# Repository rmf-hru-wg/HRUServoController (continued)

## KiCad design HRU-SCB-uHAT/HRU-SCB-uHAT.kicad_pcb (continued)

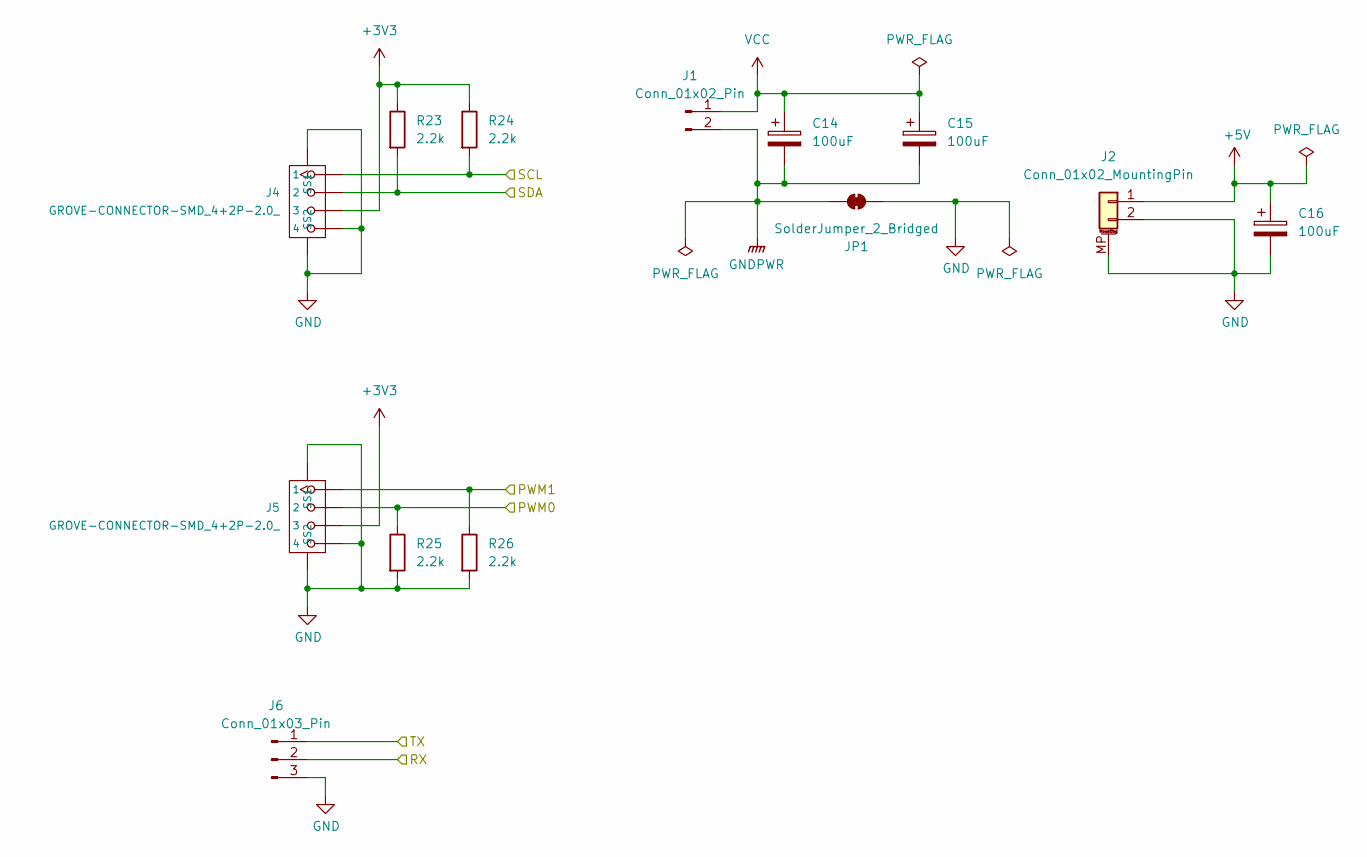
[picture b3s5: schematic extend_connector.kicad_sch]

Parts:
C14, C15, C16: 100uF; CP_EIA-6032-28_Kemet-C_HandSolder
J1: Conn_01x02_Pin; SolderWire-1.5sqmm_1x02_P7.8mm_D1.7mm_OD3.9mm
J2: Conn_01x02_MountingPin; JST_PH_B2B-PH-SM4-TB_1x02-1MP_P2.00mm_Vertical
J4, J5: GROVE-CONNECTOR-SMD_4+2P-2.0_; GROVE-HW4-SMD-2.0
J6: Conn_01x03_Pin; PinHeader_1x03_P2.54mm_Vertical
JP1: SolderJumper_2_Bridged; SolderJumper-2_P1.3mm_Bridged_Pad1.0x1.5mm
R23, R24, R25, R26: 2.2k; R_0603_1608Metric_Pad0.98x0.95mm_HandSolder

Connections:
+3V3: J4.3, J5.3, R23.1, R24.1; also elsewhere on the board
+5V: C16.1, J2.1; also elsewhere on the board
/GPIO2/SDA1: J4.2, R23.2; also elsewhere on the board
/GPIO3/SCL1: J4.1, R24.2; also elsewhere on the board
/GPIO12/PWM0: J5.2, R25.1; also elsewhere on the board
/GPIO13/PWM1: J5.1, R26.1; also elsewhere on the board
/GPIO14/TXD0: J6.1; also elsewhere on the board
/GPIO15/RXD0: J6.2; also elsewhere on the board
GND: C16.2, J2.2, J2.MP (MountPin), J4.4, J4.SS1, J4.SS2, J5.4, J5.SS1, J5.SS2, J6.3, JP1.2 (B), R25.2, R26.2; also elsewhere on the board
GNDPWR: C14.2, C15.2, J1.2, JP1.1 (A); also elsewhere on the board
VCC: C14.1, C15.1, J1.1; also elsewhere on the board

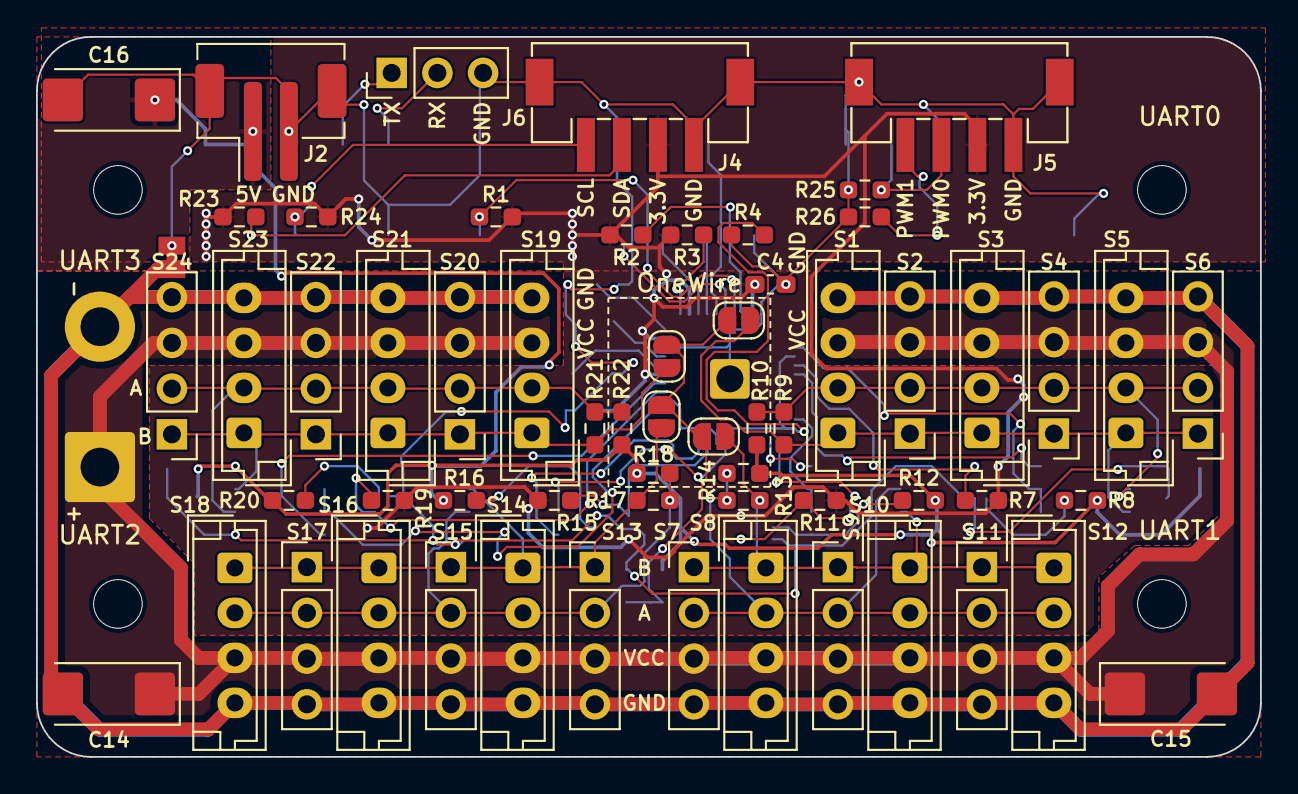
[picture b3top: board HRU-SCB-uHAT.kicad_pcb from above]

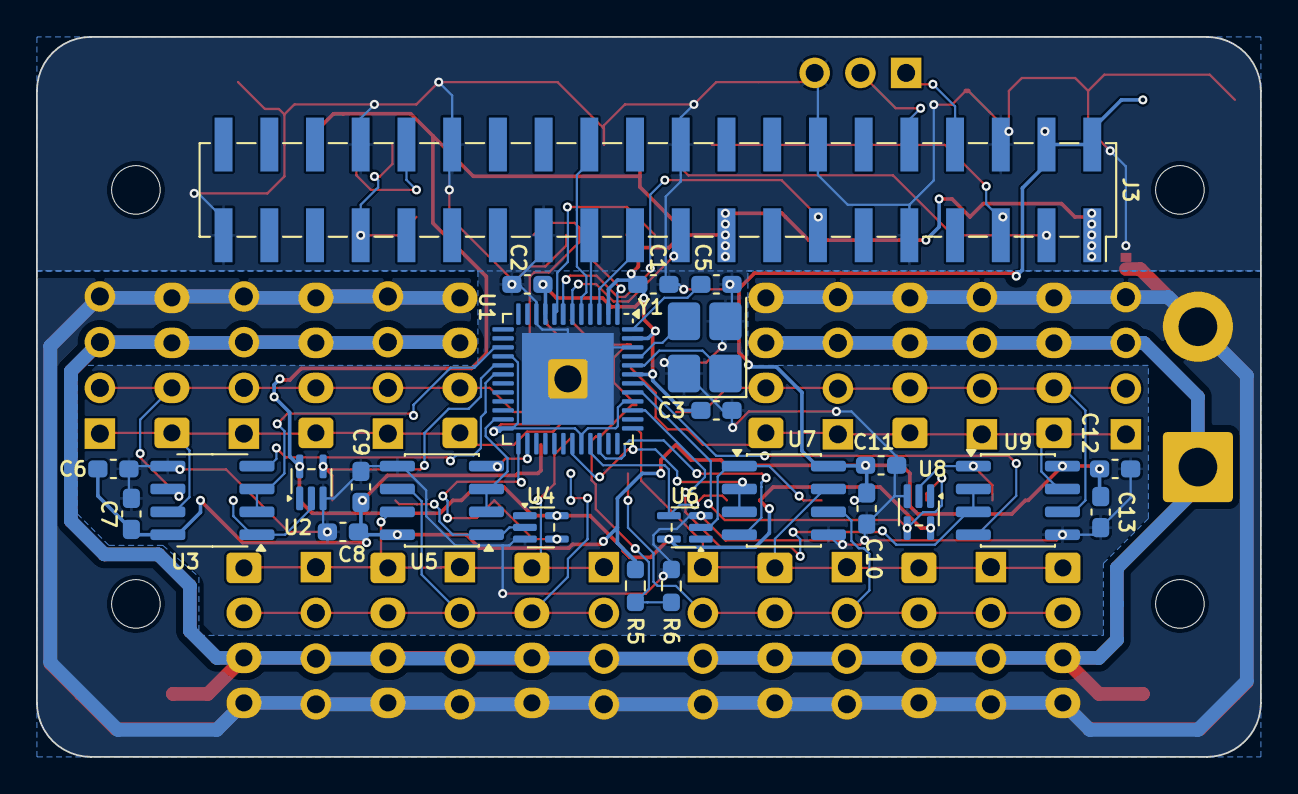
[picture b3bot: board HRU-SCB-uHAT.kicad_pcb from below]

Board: 2 copper layers, 68.0 x 40.0 mm, 91 parts (25 on the bottom side), 47 nets.

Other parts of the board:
MH1, MH2, MH3, MH4: MountingHole_2.7mm_M2.5

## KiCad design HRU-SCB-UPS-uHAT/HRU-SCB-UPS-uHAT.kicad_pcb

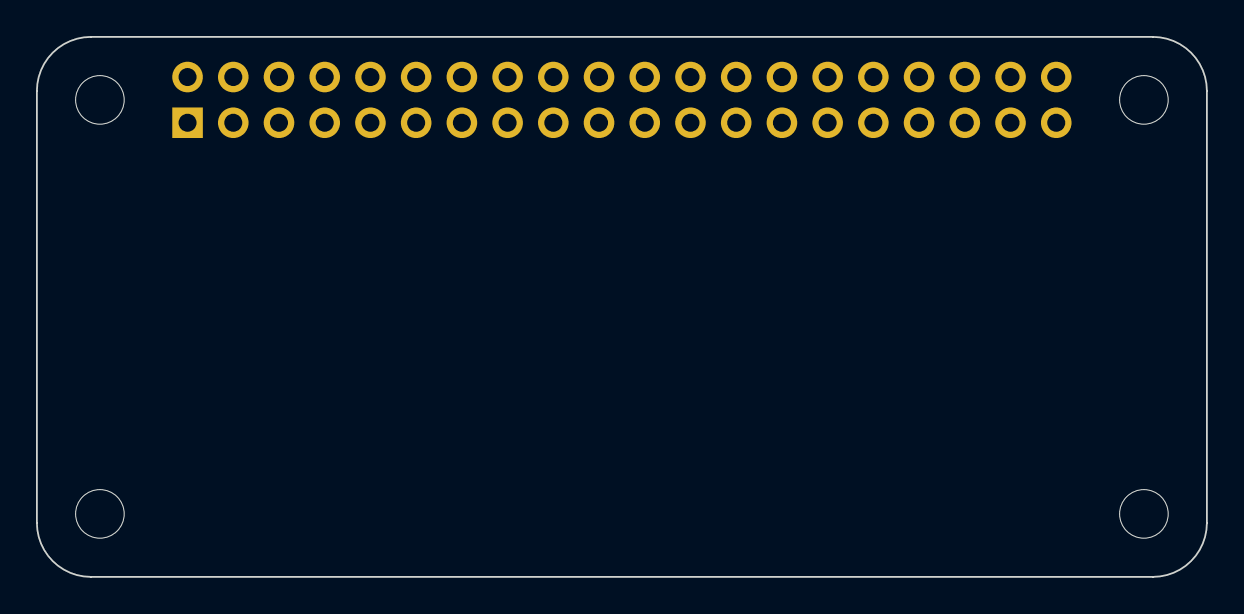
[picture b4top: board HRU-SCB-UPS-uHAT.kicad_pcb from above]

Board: 2 copper layers, 65.0 x 30.0 mm, 5 parts (1 on the bottom side), 3 nets, no tracks yet.

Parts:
J1: GPIO; PinSocket_2x20_P2.54mm_Vertical
MH1, MH2, MH3, MH4: MountingHole_2.7mm_M2.5

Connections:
+3V3: J1.1, J1.17
+5V: J1.2, J1.4
GND: J1.6, J1.9, J1.14, J1.20, J1.25, J1.30, J1.34, J1.39

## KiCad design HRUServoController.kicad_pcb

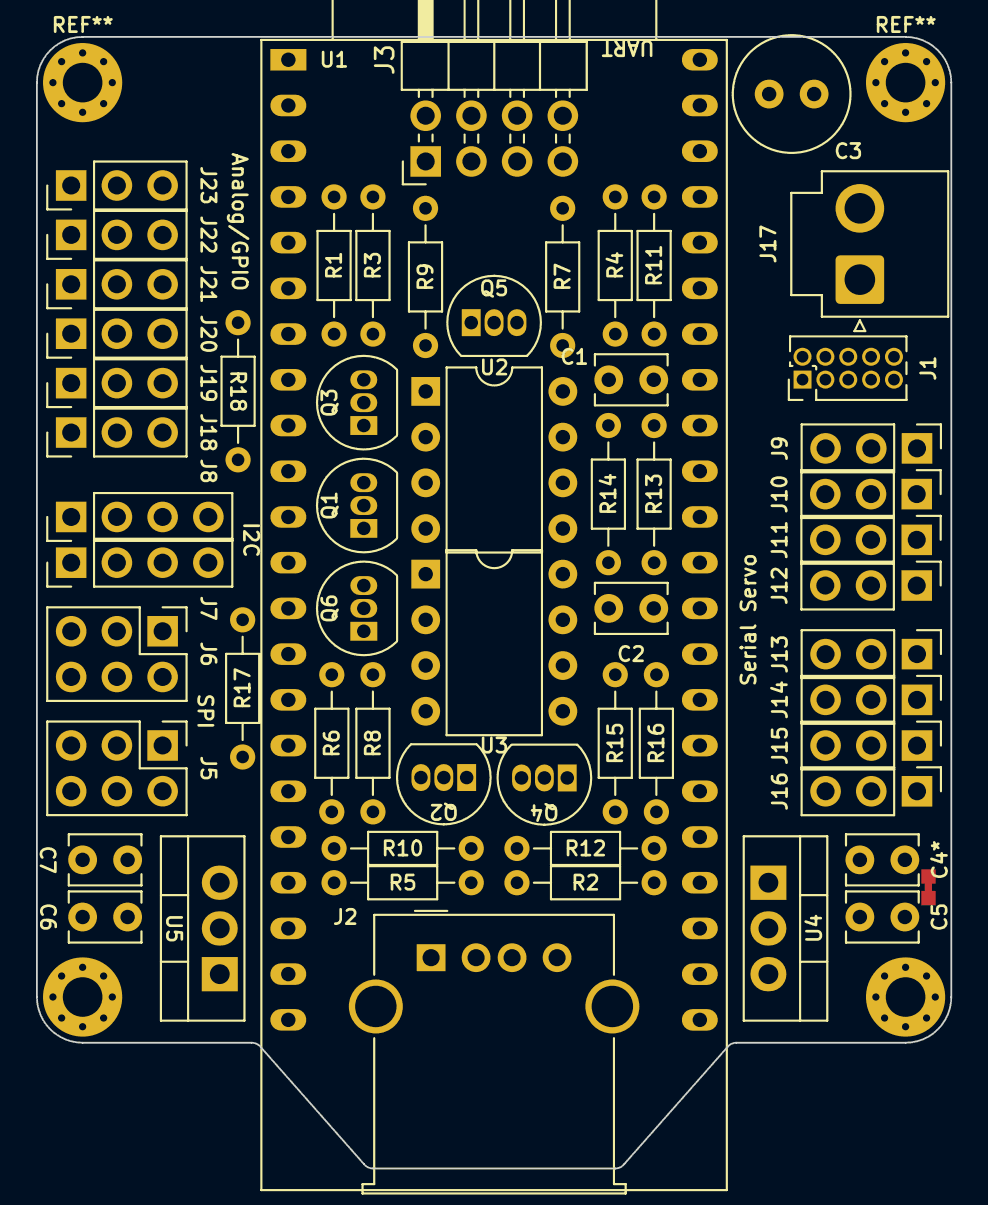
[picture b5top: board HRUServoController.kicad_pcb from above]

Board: 2 copper layers, 50.8 x 62.9 mm, 59 parts (0 on the bottom side), 42 nets, no tracks yet.

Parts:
C1, C2, C5, C6, C7: 0.1uF; C_Disc_D3.8mm_W2.6mm_P2.50mm
C3: 220u; C_Radial_D6.3mm_H11.0mm_P2.50mm
C4*: 0.33uF; C_Disc_D3.8mm_W2.6mm_P2.50mm
J1: Conn_ARM_JTAG_SWD_10; PinHeader_2x05_P1.27mm_Vertical
J2: USB_A; USB_A_Molex_67643_Horizontal
J3: Conn_02x04_Odd_Even; PinHeader_2x04_P2.54mm_Horizontal
J5, J6: Conn_02x03_Top_Bottom; PinHeader_2x03_P2.54mm_Vertical
J7, J8: Conn_01x04_Pin; PinHeader_1x04_P2.54mm_Vertical
J9, J10, J11, J12, J13, J14, J15, J16, J18, J19, J20, J21, J22, J23: Conn_01x03_Pin; PinHeader_1x03_P2.54mm_Vertical
J17: Conn_01x02_Socket; JST_VH_B2P-VH_1x02_P3.96mm_Vertical
P1: onepoint; one-point-connect
Q1, Q2, Q3, Q4, Q5, Q6: 2N7000; TO-92_Inline
R1, R2, R3, R4, R5, R6, R9, R10, R11, R12, R17, R18: 10k; R_Axial_DIN0204_L3.6mm_D1.6mm_P7.62mm_Horizontal
R7, R8, R13, R14, R15, R16: 2.2k; R_Axial_DIN0204_L3.6mm_D1.6mm_P7.62mm_Horizontal
U1: ESP32-S3-DevKitC
U2, U3: MAX485E; DIP-8_W7.62mm
U4: NJM7805FA; TO-220-3_Vertical
U5: NJU7223; TO-220-3_Vertical

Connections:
+3V3: C7.1, J1.1 (VTref), J5.5, J6.5, J7.2, J8.2, Q1.2 (G), Q2.2 (G), Q3.2 (G), Q4.2 (G), R1.2, R2.2, R3.2, R5.2, R17.1, R18.1, U1.1 (3V3), U1.2 (3V3), U5.3 (OUT)
+5V: C1.1, C2.1, C5.1, C6.1, J2.1 (VBUS), R4.2, R6.2, R9.2, R10.2, R11.2, R12.2, R13.2, R15.2, U1.21 (5V), U2.8 (VCC), U3.8 (VCC), U4.3 (OUT), U5.1 (IN)
/ADC1.CH0: J18.3, U1.41 (GPIO1/ADC1_CH0)
/ADC1.CH1: J19.3, U1.40 (GPIO2/ADC1_CH1)
/ADC1.CH3: J20.3, U1.4 (GPIO4/ADC1_CH3)
/ADC1.CH4: J21.3, U1.5 (GPIO5/ADC1_CH4)
/ADC1.CH5: J22.3, U1.6 (GPIO6/ADC1_CH5)
/ADC1.CH6: J23.3, U1.7 (GPIO7/ADC1_CH6)
/FSPI.CLK: J5.2, J6.2, U1.18 (GPIO12/ADC2_CH1)
/FSPI.CS0: J5.3, U1.16 (GPIO10/ADC1_CH9)
/FSPI.CS1: J6.3, U1.27 (GPIO21)
/FSPI.MISO: J5.1, J6.1, U1.19 (GPIO13/ADC2_CH2)
/FSPI.MOSI: J5.4, J6.4, U1.17 (GPIO11/ADC2_CH0)
/I2C.SCL: J7.4, J8.4, R18.2, U1.15 (GPIO9/ADC1_CH8)
/I2C.SDA: J7.3, J8.3, R17.2, U1.12 (GPIO8/ADC1_CH7)
/IOPort/SERVO1.SIG: J9.3, J10.3, J11.3, J12.3, U2.6 (A)
/IOPort/SERVO2.SIG: J13.3, J14.3, J15.3, J16.3, U3.6 (A)
/MTCK: J1.4 (SWDCLK/TCK), U1.36 (GPIO39/MTCK)
/MTDI: J1.8 (NC/TDI), U1.38 (GPIO41/MTDI)
/MTDO: J1.6 (SWO/TDO), U1.37 (GPIO40/MTDO)
/MTMS: J1.2 (SWDIO/TMS), U1.39 (GPIO42/MTMS)
/UART1.RX: J3.5, Q3.1 (S), R3.1, U1.11 (GPIO18/ADC2_CH7)
/UART1.TX: J3.7, Q1.1 (S), R1.1, U1.10 (GPIO17/ADC2_CH6)
/UART2.RX: J3.6, Q4.1 (S), R5.1, U1.29 (GPIO48)
/UART2.TX: J3.8, Q2.1 (S), R2.1, U1.28 (GPIO47)
/USB_DN: J2.2 (D-), U1.25 (GPIO19/USB_D-)
/USB_DP: J2.3 (D+), U1.26 (GPIO20/USB_D+)
/~RESET: J1.10 (~RESET), U1.3 (CHIP_PU)
GND: C1.2, C2.2, C5.2, C6.2, C7.2, J1.3 (GND), J1.5 (GND), J1.9 (GNDDetect), J2.4 (GND), J2.5 (Shield), J3.1, J3.2, J5.6, J6.6, J7.1, J8.1, J9.1, J10.1, J11.1, J12.1, J13.1, J14.1, J15.1, J16.1, J18.1, J19.1, J20.1, J21.1, J22.1, J23.1, P1.2, Q5.1 (S), Q6.1 (S), R14.1, R16.1, U2.5 (GND), U3.5 (GND), U5.2 (GND)
GNDPWR: C3.2, C4*.2, J17.2, P1.1, U4.2 (GND)
unnamed: Q1.3 (D), R4.1, R7.1, U2.4 (DI)
unnamed: Q2.3 (D), R6.1, R8.1, U3.4 (DI)
unnamed: Q3.3 (D), R9.1, U2.1 (RO)
unnamed: Q4.3 (D), R10.1, U3.1 (RO)
unnamed: Q5.3 (D), R11.1, U2.2 (~RE), U2.3 (DE)
unnamed: Q5.2 (G), R7.2
unnamed: Q6.3 (D), R12.1, U3.2 (~RE), U3.3 (DE)
unnamed: Q6.2 (G), R8.2
unnamed: U1.22 (GND), U1.23 (GND), U1.24 (GND), U1.44 (GND)
unnamed: R13.1, R14.2, U2.7 (B)
unnamed: R15.1, R16.2, U3.7 (B)
VCC: C3.1, C4*.1, J3.3, J3.4, J9.2, J10.2, J11.2, J12.2, J13.2, J14.2, J15.2, J16.2, J17.1, J18.2, J19.2, J20.2, J21.2, J22.2, J23.2, U4.1 (IN)

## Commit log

2023-09-09 Baseline
2023-09-10 Commit prototype design using ESP32-S3
2024-04-14 Update design for hand soldering friendly
2024-04-14 Create LICENSE
2024-07-20 Update DCDC for DIP soldering
2024-09-06 Modify footprint of the registers and regulators
2025-11-23 feat(Raspi-HAT): Initial commit of Raspi HAT Board
2025-12-19 update: .gitignore
2025-12-19 update: circuit design of HRU-SCB-RP2040
2026-02-07 Update: fix parts layout
2026-02-08 Update: fix ERC error
2026-02-09 Update: routed wires
2026-03-08 Fix: MAX14830 version
2026-03-18 Add: M5Atom entry board (draft)
2026-03-18 Update: parts layout and smaller board
2026-03-18 Update: M5Atom entry board with Grove port
2026-03-18 Move: change file path of Raspi board using MAX14830 (SPI to UART)
2026-03-29 Update: apply super DCDC
2026-03-29 update: non-via circuit
2026-03-31 update: larger board outline for flesh members
2026-05-04 Update: PCB wires
2026-05-24 fix(HRU-SCB-RP2040): add diodes for level shift
2026-06-07 fix(HRU-SCB-RP2040): assign 3V3 to I2C's VCC and refactor parts layout
